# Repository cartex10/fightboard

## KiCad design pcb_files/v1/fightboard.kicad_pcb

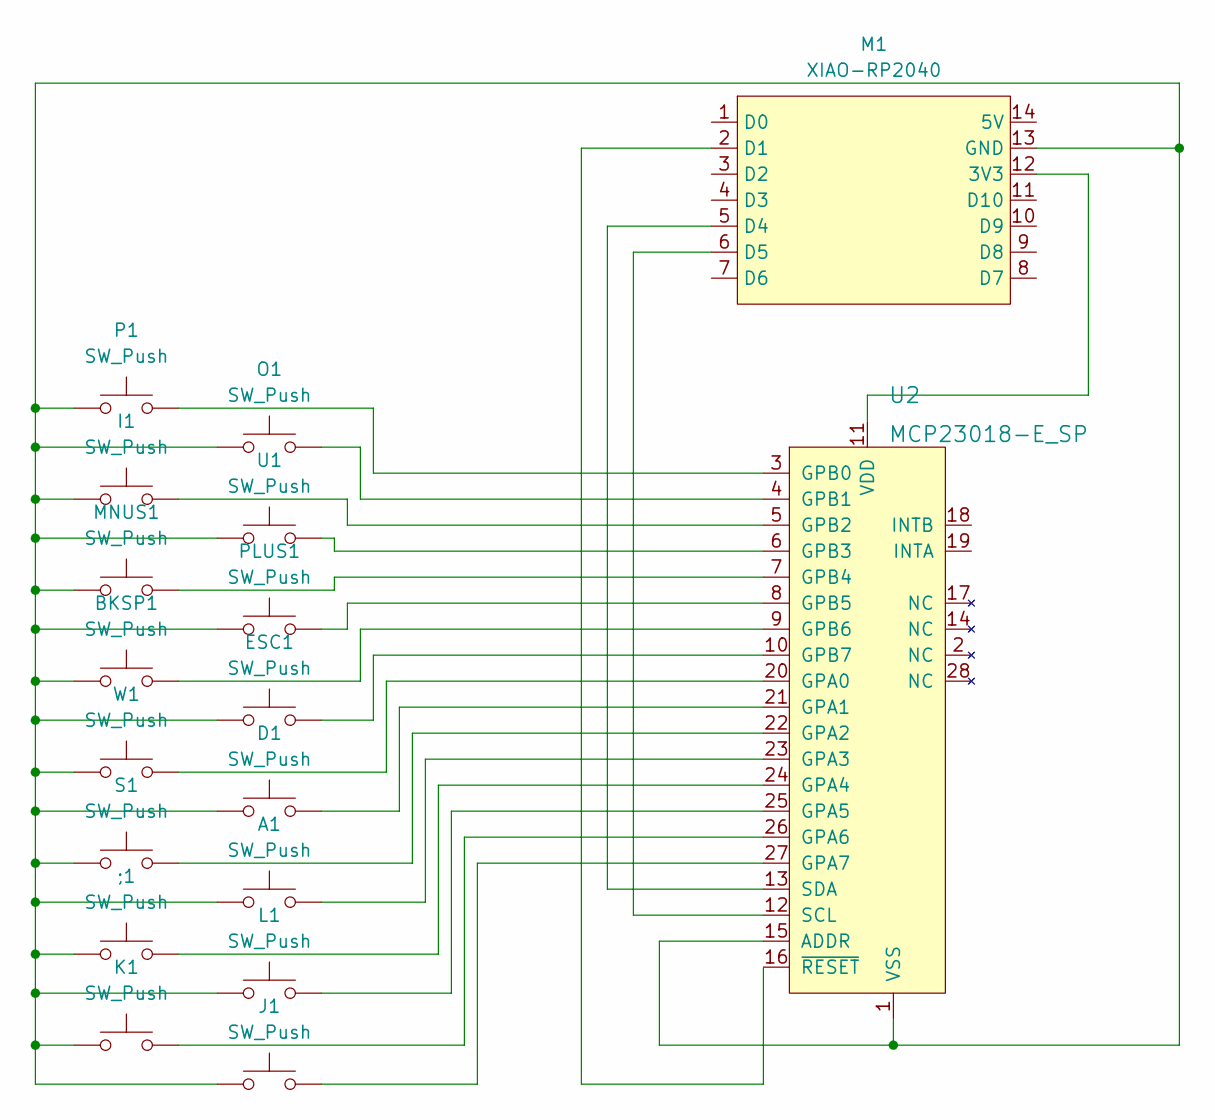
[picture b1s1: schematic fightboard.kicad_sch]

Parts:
;1: SW_Push; Kailh_socket_MX
A1: SW_Push; Kailh_socket_MX
BKSP1: SW_Push; SW_PUSH_6mm
D1: SW_Push; Kailh_socket_MX
ESC1: SW_Push; SW_PUSH_6mm
I1: SW_Push; Kailh_socket_MX
J1: SW_Push; Kailh_socket_MX
K1: SW_Push; Kailh_socket_MX
L1: SW_Push; Kailh_socket_MX
M1: XIAO-RP2040
MNUS1: SW_Push; SW_PUSH_6mm
O1: SW_Push; Kailh_socket_MX
P1: SW_Push; Kailh_socket_MX
PLUS1: SW_Push; SW_PUSH_6mm
S1: SW_Push; Kailh_socket_MX
U1: SW_Push; Kailh_socket_MX
U2: MCP23018-E_SP; DIP-28_W7.62mm; MPN MCP23018-E/SP; Digi-Key_PN MCP23018-E/SP-ND
W1: SW_Push; Kailh_socket_MX

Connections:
unnamed: ;1.1, A1.1, BKSP1.1, D1.1, ESC1.1, I1.1, J1.1, K1.1, L1.1, M1.13 (GND), MNUS1.1, O1.1, P1.1, PLUS1.1, S1.1, U1.1, U2.1 (VSS), U2.15 (ADDR), W1.1
unnamed: ;1.2, U2.24 (GPA4)
unnamed: A1.2, U2.23 (GPA3)
unnamed: BKSP1.2, U2.9 (GPB6)
unnamed: D1.2, U2.21 (GPA1)
unnamed: ESC1.2, U2.10 (GPB7)
unnamed: I1.2, U2.5 (GPB2)
unnamed: J1.2, U2.27 (GPA7)
unnamed: K1.2, U2.26 (GPA6)
unnamed: L1.2, U2.25 (GPA5)
unnamed: M1.2 (D1), U2.16 (~RESET)
unnamed: M1.5 (D4), U2.13 (SDA)
unnamed: M1.6 (D5), U2.12 (SCL)
unnamed: M1.12 (3V3), U2.11 (VDD)
unnamed: MNUS1.2, U2.7 (GPB4)
unnamed: O1.2, U2.4 (GPB1)
unnamed: P1.2, U2.3 (GPB0)
unnamed: PLUS1.2, U2.8 (GPB5)
unnamed: S1.2, U2.22 (GPA2)
unnamed: U1.2, U2.6 (GPB3)
unnamed: U2.20 (GPA0), W1.2

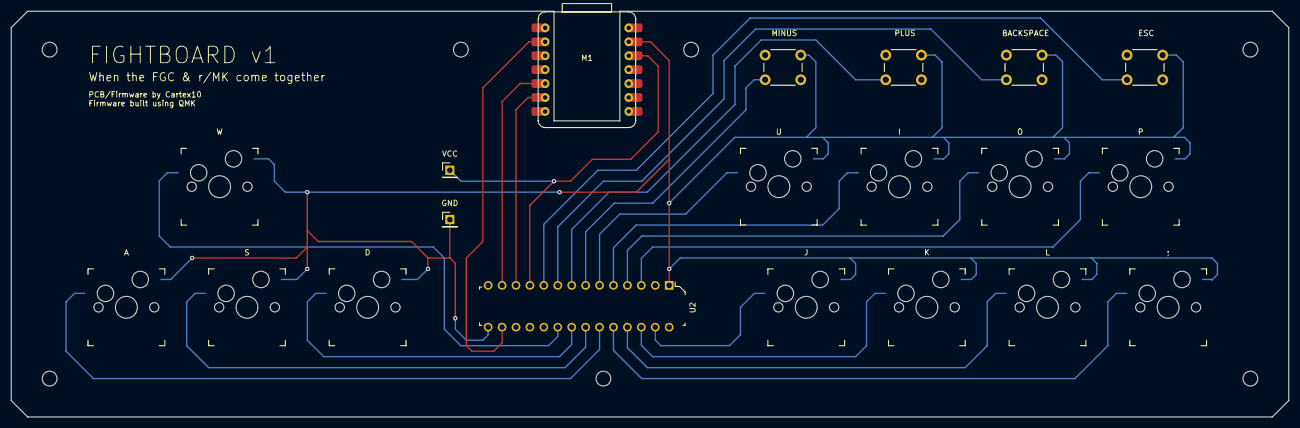
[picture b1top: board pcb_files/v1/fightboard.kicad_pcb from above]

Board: 2 copper layers, 233.0 x 74.0 mm, 18 parts (0 on the bottom side), 21 nets.

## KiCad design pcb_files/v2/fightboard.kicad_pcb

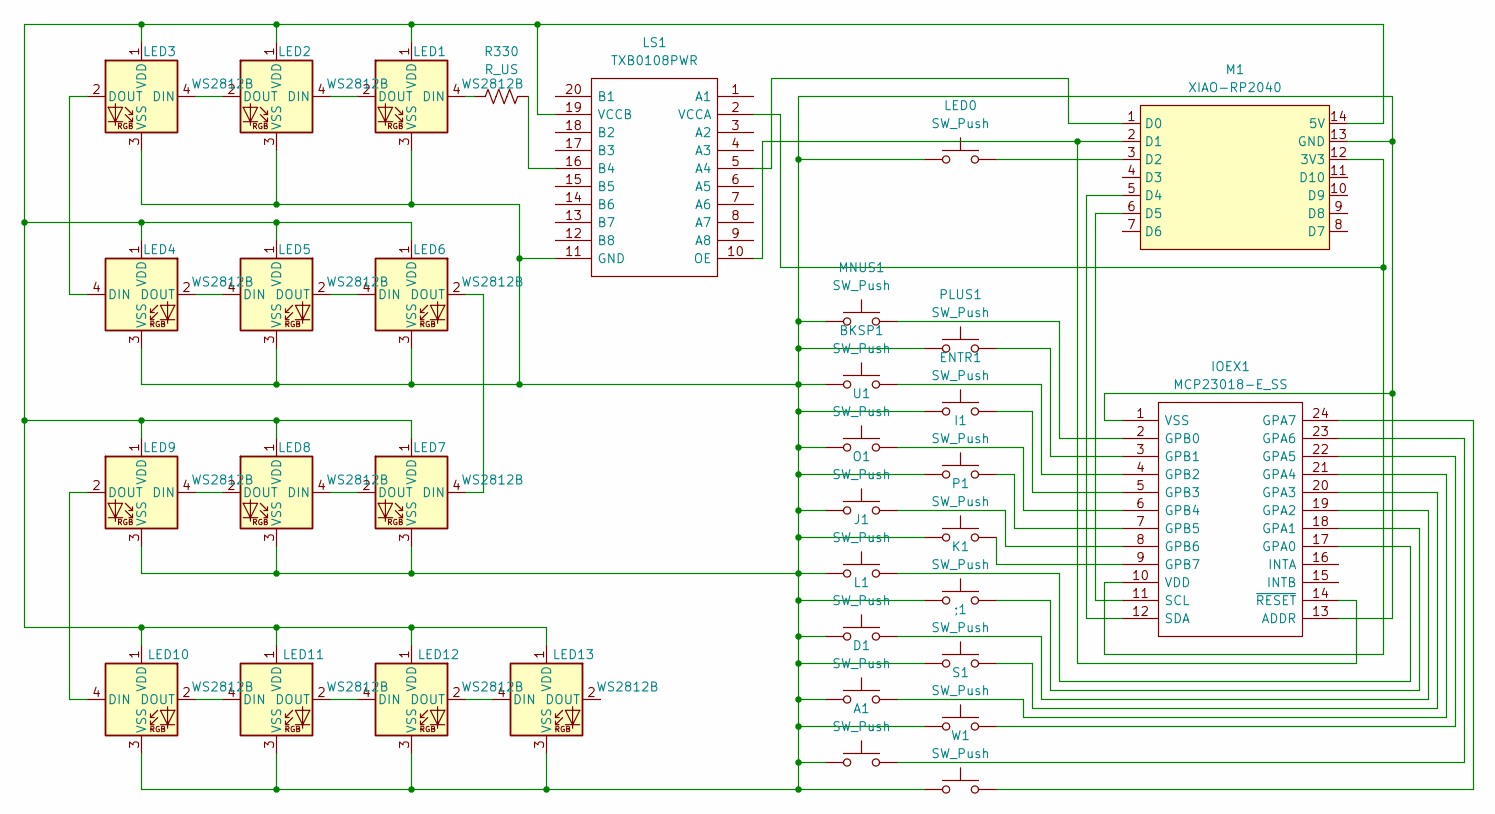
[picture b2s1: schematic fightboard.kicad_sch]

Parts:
;1: SW_Push; mx-choc socket keyswitch
A1: SW_Push; mx-choc socket keyswitch
BKSP1: SW_Push; SW_PUSH_6mm
D1: SW_Push; mx-choc socket keyswitch
ENTR1: SW_Push; SW_PUSH_6mm
I1: SW_Push; mx-choc socket keyswitch
IOEX1: MCP23018-E_SS; SOP65P780X200-24N; Mouser Part Number 579-MCP23018-E/SS
J1: SW_Push; mx-choc socket keyswitch
K1: SW_Push; mx-choc socket keyswitch
L1: SW_Push; mx-choc socket keyswitch
LED0: SW_Push; SW_PUSH_6mm
LED1, LED2, LED3, LED4, LED5, LED6, LED7, LED8, LED9, LED10, LED11, LED12, LED13: WS2812B; Reverse Mount SK6812MINI-E
LS1: TXB0108PWR; SOP65P640X120-20N; Mouser Part Number 595-TXB0108PWR
M1: XIAO-RP2040
MNUS1: SW_Push; SW_PUSH_6mm
O1: SW_Push; mx-choc socket keyswitch
P1: SW_Push; mx-choc socket keyswitch
PLUS1: SW_Push; SW_PUSH_6mm
R330: R_US; R_2010_5025Metric_Pad1.40x2.65mm_HandSolder
S1: SW_Push; mx-choc socket keyswitch
U1: SW_Push; mx-choc socket keyswitch
W1: SW_Push; mx-choc socket keyswitch

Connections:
unnamed: ;1.1, A1.1, BKSP1.1, D1.1, ENTR1.1, I1.1, IOEX1.1 (VSS), IOEX1.13 (ADDR), J1.1, K1.1, L1.1, LED0.1, LED1.3 (VSS), LED2.3 (VSS), LED3.3 (VSS), LED4.3 (VSS), LED5.3 (VSS), LED6.3 (VSS), LED7.3 (VSS), LED8.3 (VSS), LED9.3 (VSS), LED10.3 (VSS), LED11.3 (VSS), LED12.3 (VSS), LED13.3 (VSS), LS1.11 (GND), M1.13 (GND), MNUS1.1, O1.1, P1.1, PLUS1.1, S1.1, U1.1, W1.1
unnamed: IOEX1.17 (GPA0), J1.2
unnamed: IOEX1.18 (GPA1), K1.2
unnamed: IOEX1.19 (GPA2), L1.2
unnamed: ;1.2, IOEX1.20 (GPA3)
unnamed: D1.2, IOEX1.21 (GPA4)
unnamed: IOEX1.22 (GPA5), S1.2
unnamed: A1.2, IOEX1.23 (GPA6)
unnamed: IOEX1.24 (GPA7), W1.2
unnamed: IOEX1.2 (GPB0), MNUS1.2
unnamed: IOEX1.3 (GPB1), PLUS1.2
unnamed: BKSP1.2, IOEX1.4 (GPB2)
unnamed: ENTR1.2, IOEX1.5 (GPB3)
unnamed: IOEX1.6 (GPB4), U1.2
unnamed: I1.2, IOEX1.7 (GPB5)
unnamed: IOEX1.8 (GPB6), O1.2
unnamed: IOEX1.9 (GPB7), P1.2
unnamed: IOEX1.11 (SCL), M1.6 (D5)
unnamed: IOEX1.12 (SDA), M1.5 (D4)
unnamed: IOEX1.10 (VDD), LS1.2 (VCCA), M1.12 (3V3)
unnamed: IOEX1.14 (~RESET), LS1.10 (OE), M1.2 (D1)
unnamed: LED1.4 (DIN), R330.1
unnamed: LED1.2 (DOUT), LED2.4 (DIN)
unnamed: LED1.1 (VDD), LED2.1 (VDD), LED3.1 (VDD), LED4.1 (VDD), LED5.1 (VDD), LED6.1 (VDD), LED7.1 (VDD), LED8.1 (VDD), LED9.1 (VDD), LED10.1 (VDD), LED11.1 (VDD), LED12.1 (VDD), LED13.1 (VDD), LS1.19 (VCCB), M1.14 (5V)
unnamed: LED2.2 (DOUT), LED3.4 (DIN)
unnamed: LED3.2 (DOUT), LED4.4 (DIN)
unnamed: LED4.2 (DOUT), LED5.4 (DIN)
unnamed: LED5.2 (DOUT), LED6.4 (DIN)
unnamed: LED6.2 (DOUT), LED7.4 (DIN)
unnamed: LED7.2 (DOUT), LED8.4 (DIN)
unnamed: LED8.2 (DOUT), LED9.4 (DIN)
unnamed: LED9.2 (DOUT), LED10.4 (DIN)
unnamed: LED10.2 (DOUT), LED11.4 (DIN)
unnamed: LED11.2 (DOUT), LED12.4 (DIN)
unnamed: LED12.2 (DOUT), LED13.4 (DIN)
unnamed: LS1.5 (A4), M1.1 (D0)
unnamed: LS1.16 (B4), R330.2
unnamed: LED0.2, M1.3 (D2)

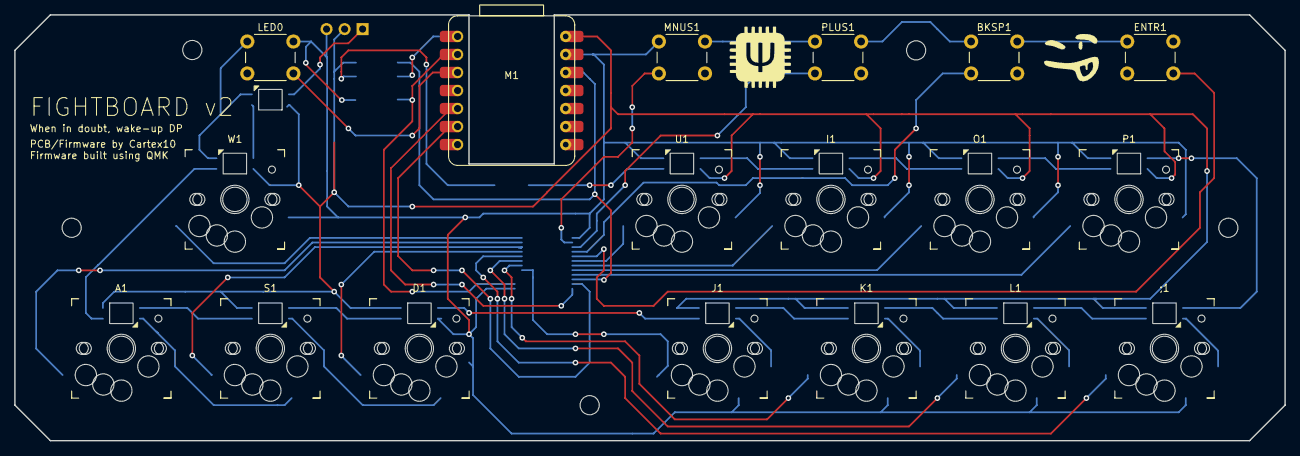
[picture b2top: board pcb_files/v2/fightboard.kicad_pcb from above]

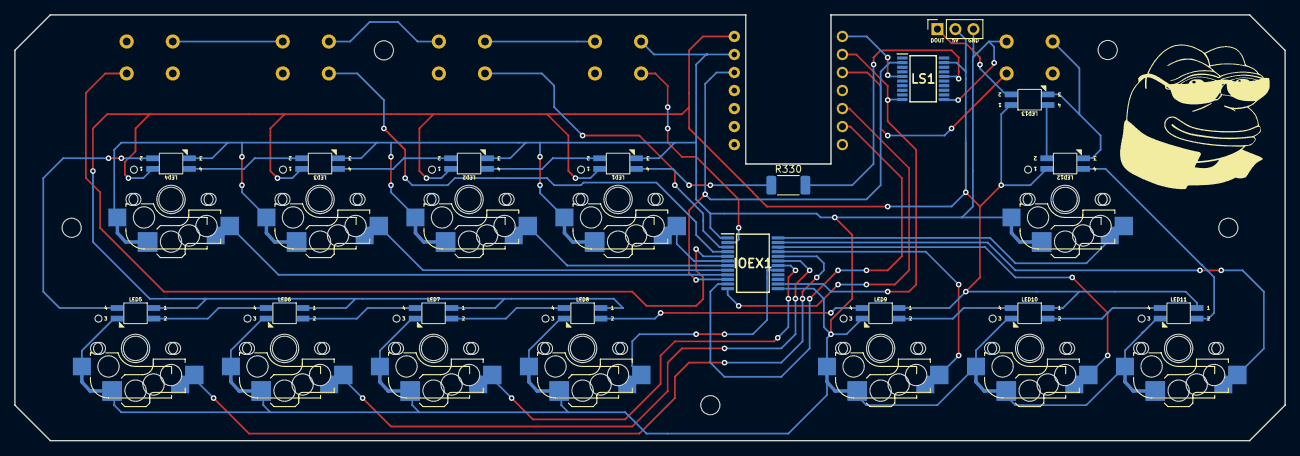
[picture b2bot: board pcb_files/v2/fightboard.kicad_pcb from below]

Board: 2 copper layers, 179.0 x 60.0 mm, 34 parts (3 on the bottom side), 38 nets.

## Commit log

2022-08-16 10 button direct pin config
2022-08-16 init commit
2022-08-16 pcb design with mcp23018
2022-08-16 add finishing touches to prev design
2022-08-20 add mcp io extender to firmware, along with 6 more buttons
2022-08-20 change enter to esc
2022-09-04 new firmware for mcp23018
2022-09-04 update pcb
2022-09-11 fix default layout to fit pcb
2022-09-11 add player 2 keymap
2022-10-01 update player2 keymap
2022-10-13 add rgb functions
2022-10-13 remove unnecessary files
2022-10-26 update rgb functions, still needs work
2022-11-04 further rgb fix
2022-11-04 move pcb files into v1 folder
2022-11-05 add v2 schematic
2022-11-09 separate v1 firmware from v2
2022-11-09 add v2 pcb
2022-11-29 migrate from rgblight to rgbmatrix
2022-11-29 edit keybinds
2022-11-30 update v2 pcb
2022-11-30 i forgor (this file)
2022-12-06 update pcb with led extension pins
2022-12-06 add LED indicator function
2022-12-13 add software configurable SOCD
2022-12-13 fix errors with pcb
2022-12-13 finish fixing errors
2022-12-13 update RGB effects/binds, redo layers
2022-12-14 update firmware for PCB, and finish layer selection/indication
2022-12-16 fix issues that arose with final install
2022-12-16 update v1 for newest QMK version
2022-12-23 prepare to support QMK configurator
2022-12-23 layer from last shutdown is now saved to eeprom and accessed on startup
2022-12-23 clean up
2023-01-09 add xinput files, dont work at all
2023-06-19 remove capacitors
2023-06-19 small fixes
2024-02-01 add secondary SOCD and update config
